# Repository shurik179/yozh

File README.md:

# Yozh Robot
Yozh is a small tracked  robot programmable in CircuitPython. 
It was  inspired by  Pololu's Zumo, but has numerous improvements over it. 
It was created by shurik179 for a robotics class at SigmaCamp.

The project description and logs are posted on Hackaday: 
https://hackaday.io/project/193665-yozh-robot. 
Detailed  user documentation is available at http://yozh.rtfd.io. 

## Status
Version 4 is mostly finished, working on documentation and fine-tuning 
various PID controllers. 

## Structure of this repository
* `docs`: documentation (used to produce docs at http://yozh.rtfd.io)
* `hardware`: design files for the custom electronics boards, BOM, etc.
* `board_support_package`: bootloader and packeg to have the secondary MCU 
   supported in Arduino IDE. Only needed fro uploading the firmware - end 
   users do not need this. 
* `firmware`: firmware for secondary MCU
* `circuitpython_library`: Circuit Python user library

## License
Ecept as noted below, all components (hardware, software, documentation) are
copyright by Alexander Kirillov  and are  released under MIT license.
See file LICENSE in this directory for full text of the license.

Circuit Python librabries included in circuitpython_library/lib are copyright by Adafruit, see
https://github.com/adafruit/Adafruit_CircuitPython_Bundle . They are released under MIT License.

Fonts included with Circuit Python library are released under SIL Open Font License.
See LICENSE file in directory circuitpython_library/fonts

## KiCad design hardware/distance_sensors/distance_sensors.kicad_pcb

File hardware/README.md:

# Hardware components for Yozh

This directory contains various hardware design files for Yozh. It includes
the following files and directories:

* `mainboard`: directory with design files for the main electronics board
* `spacer`: design files for the  spacer,  which goes between the main board and the chassis
* `reflectance_sensor_array`: design files for the reflectance sensor array   
* `top_plate`, `top_plate-LSM6`: design files for two different versions of the  
   top plate, containingin OLED display, buttons, and IMU. Current version of
   the robot uses `top_plate-LSM6`, which is based on LSM6DSL 6 degree of freedom
   Inertial Motion Unit.
   Folder `top_plate` contains design based on ICM42968 9DOF IMU; this is work in progress to be used in future versions.
* `front_sensors`: design files for  the removable board containing the two front-facing distance sensors
* `blade.dxf`: the DXF file of the front blade. This blade is to be lasercut
  from 0.030" stainless steel (you can use Pololu [laser-cutting service](https://www.pololu.com/product/749)  for it. )
* `pins.xlsx`: spreadsheet listing all pins of SAMD21 MCU and their use
* `board frame.stl`: STL file of the 3d printed holder I used to hold the mainboard
   for stenciling solder paste

Each design directory contains KiCad 6.0  design files, BOM, and gerbers.  
I assembled the mainboard myself; the top plate, reflectance sensor array, and front sensor board I ordered assembled from JLCPCB. These directories  have two versions of BOM: general and for JLCPCB assembly.

All PCBs use 1.6mm thickness, black soldermask and white screen. The main board
is a 4-layer PCB, all others are 2-layer.

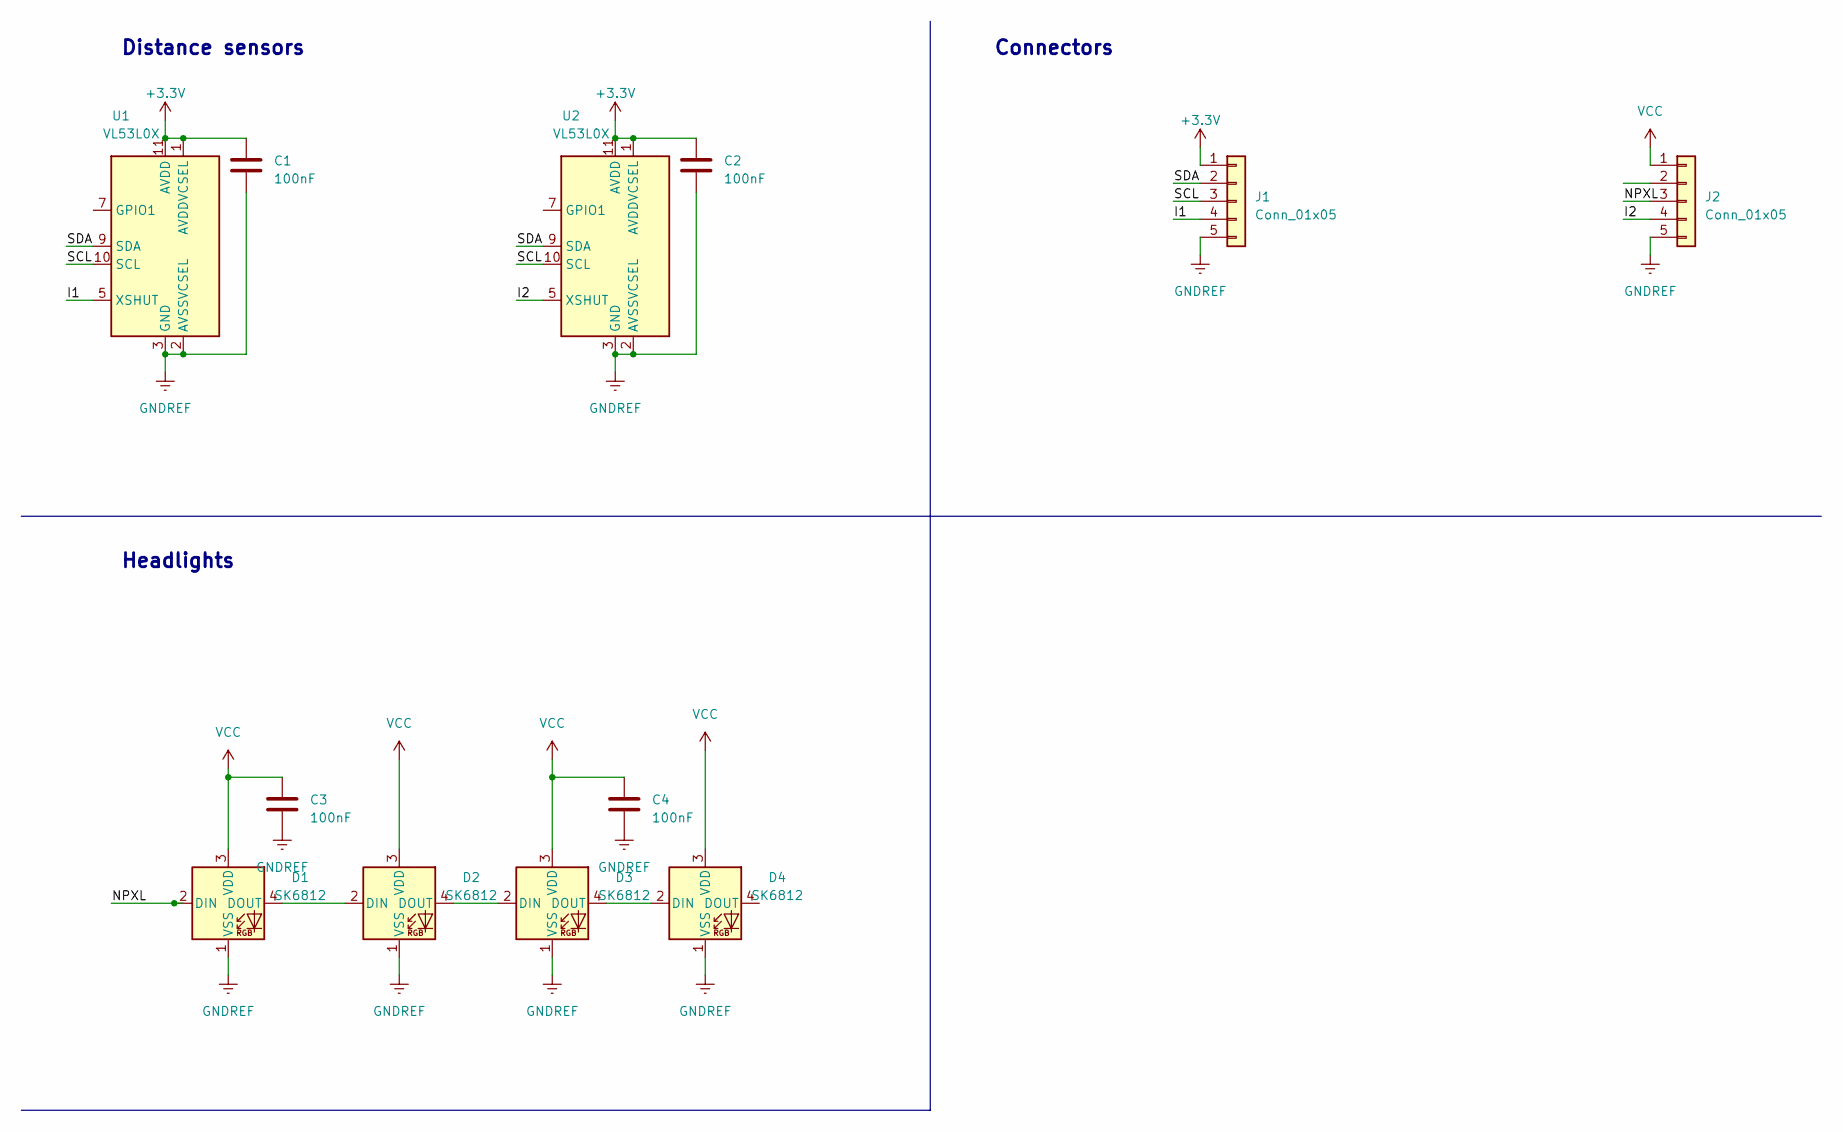
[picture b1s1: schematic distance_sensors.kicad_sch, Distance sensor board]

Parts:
C1, C2, C3, C4: 100nF; C_0603_1608Metric; LCSC C14663
D1, D2, D3, D4: SK6812; LED_SK6812_PLCC4_5.0x5.0mm_P3.2mm
J1, J2: Conn_01x05; PinSocket_1x05_P2.54mm_Vertical
U1, U2: VL53L0X; ST_VL53L1x; LCSC C91199

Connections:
+3V3: C1.1, C2.1, J1.1, U1.1 (AVDDVCSEL), U1.11 (AVDD), U2.1 (AVDDVCSEL), U2.11 (AVDD)
/I1: J1.4, U1.5 (XSHUT)
/I2: J2.4, U2.5 (XSHUT)
/NPXL: D1.2 (DIN), J2.3
/SCL: J1.3, U1.10 (SCL), U2.10 (SCL)
/SDA: J1.2, U1.9 (SDA), U2.9 (SDA)
GNDREF: C1.2, C2.2, C3.2, C4.2, D1.1 (VSS), D2.1 (VSS), D3.1 (VSS), D4.1 (VSS), J1.5, J2.5, U1.2 (AVSSVCSEL), U1.3 (GND), U1.4 (GND), U1.6 (GND), U1.12 (GND), U2.2 (AVSSVCSEL), U2.3 (GND), U2.4 (GND), U2.6 (GND), U2.12 (GND)
unnamed: D1.4 (DOUT), D2.2 (DIN)
unnamed: D2.4 (DOUT), D3.2 (DIN)
unnamed: D3.4 (DOUT), D4.2 (DIN)
VCC: C3.1, C4.1, D1.3 (VDD), D2.3 (VDD), D3.3 (VDD), D4.3 (VDD), J2.1

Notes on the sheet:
Distance sensors
Connectors
Headlights

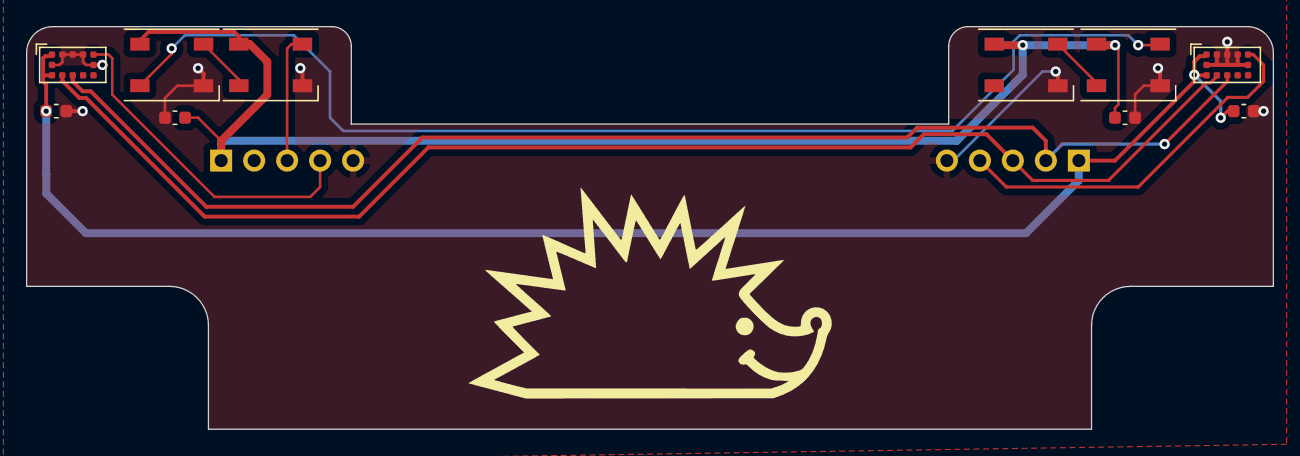
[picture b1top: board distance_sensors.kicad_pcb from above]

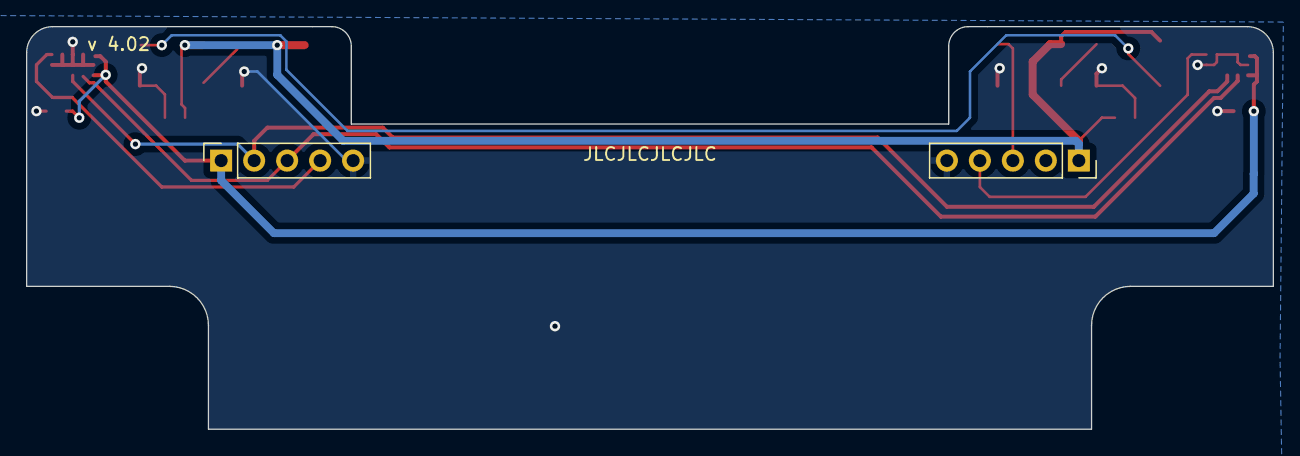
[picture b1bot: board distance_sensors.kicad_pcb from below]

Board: 2 copper layers, 96.0 x 31.0 mm, 12 parts (2 on the bottom side), 11 nets.

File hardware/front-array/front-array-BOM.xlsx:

Component | Description | Part Number | References | Value | Footprint | Quantity Per PCB | Side | Datasheet | LCSC | Comment
1 | SMD capacitor, 0603, 100nF |  | C1 C2 | 100nF | C_0603_1608Metric | 2 | Top | ~ | C14663
2 | 1x5 female header, 90 deg, 0.1" |  | J1 J2 | Conn_01x05 | PinSocket_1x05_P2.54mm_Horizontal | 2 | Top | ~
3 | 2m distance ranging ToF sensor | VL53L0X | U1 U2 | VL53L0X | LGA12 | 2 | Top | https://www.st.com/resource/en/datasheet/vl53l0x.pdf | C91199

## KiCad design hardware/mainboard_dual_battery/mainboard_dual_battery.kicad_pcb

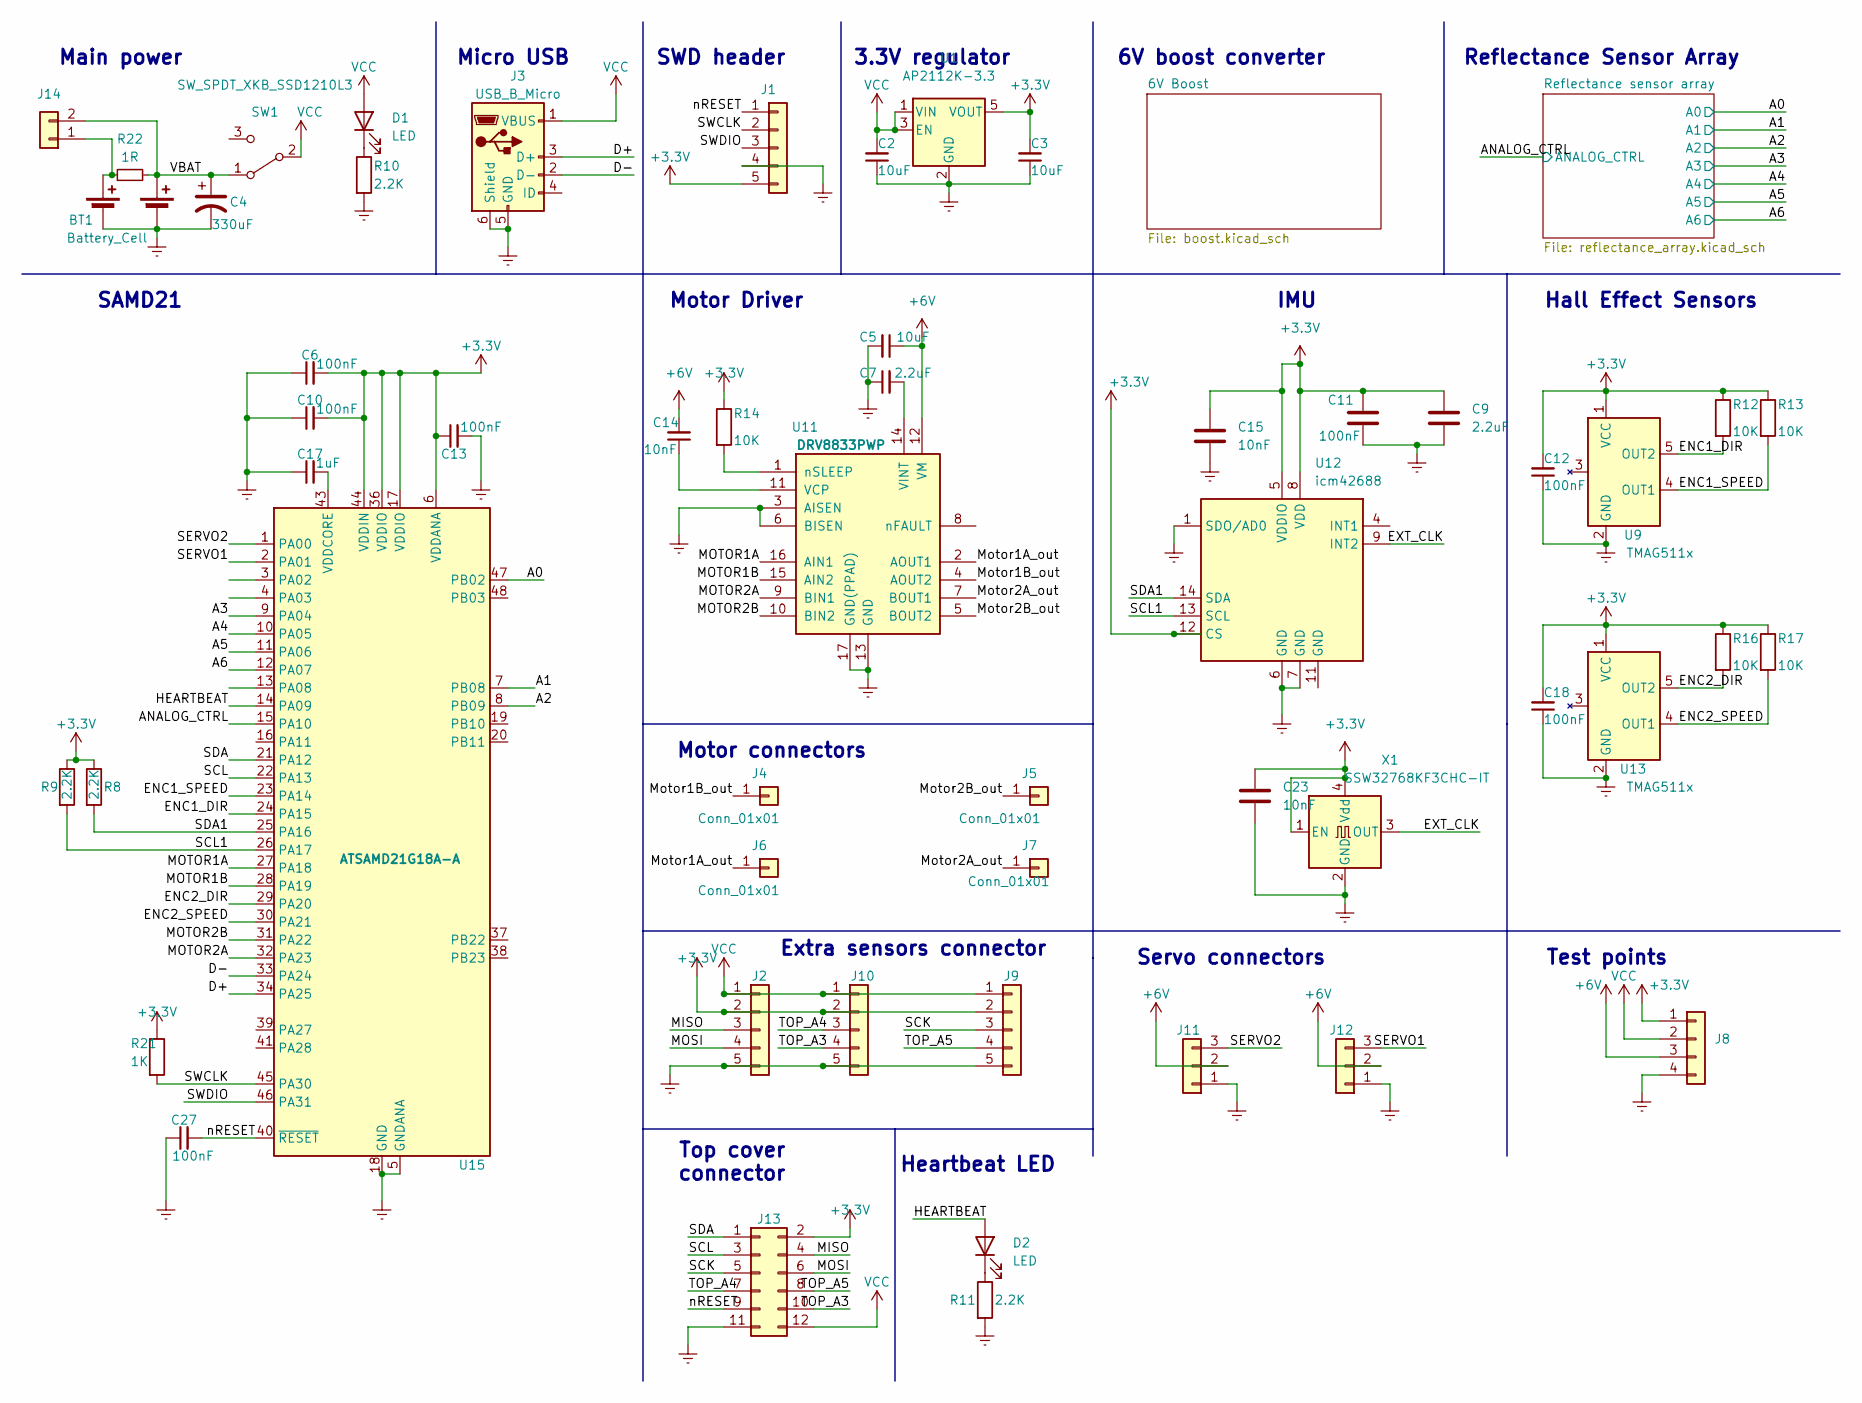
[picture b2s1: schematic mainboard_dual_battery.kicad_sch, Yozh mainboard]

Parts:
BT1: Battery_Cell; BatteryHolder_MYOUNG_BH-18650-B1BA007_2x18650; LCSC C6937126
C2, C3, C5: 10uF; C_0805_2012Metric; LCSC C15850
C4: 330uF; CP_Elec_6.3x7.7; LCSC C2980164
C6, C10, C11, C12, C13, C18, C27: 100nF; C_0603_1608Metric; LCSC C14663
C7, C9: 2.2uF; C_0603_1608Metric; LCSC C23630
C14, C15, C23: 10nF; C_0603_1608Metric; LCSC C57112
C17: 1uF; C_0603_1608Metric; LCSC C15849
D1, D2: LED; LED_0603_1608Metric; LCSC C72043
J1: Conn_01x05; PinSocket_1x05_P2.54mm_Lock
J2, J9, J10: Conn_01x05; PinHeader_1x05_P2.54mm_Vertical; LCSC C492404
J3: USB_B_Micro; USB_Micro-B_Amphenol_10118194_Horizontal; LCSC C132563
J4, J5, J6, J7: Conn_01x01; connector-1p-generic-nosilk
J8: Conn_01x04; connector-4p-generic-nosilk
J11, J12: Conn_01x03; PinHeader_1x03_P2.54mm_Vertical; LCSC C49257
J13: Conn_02x06_Odd_Even; PinSocket_2x06_P2.54mm_Vertical; LCSC C541855
J14: Conn_01x02; PinHeader_1x02_P2.54mm_Vertical
R8, R9, R10, R11: 2.2K; R_0603_1608Metric; LCSC C4190
R12, R13, R14, R16, R17: 10K; R_0603_1608Metric; LCSC C25804
R21: 1K; R_0603_1608Metric; LCSC C21190
R22: 1R; R_0603_1608Metric; LCSC C22936
SW1: SW_SPDT_XKB_SSD1210L3; SW_XKB_SS12D10L3; LCSC C319013
U1: AP2112K-3.3; SOT-23-5; LCSC C51118
U9, U13: TMAG511x; SOT-23-5
U11: DRV8833PWP; HTSSOP-16-1EP_4.4x5mm_P0.65mm_EP3.4x5mm_Mask2.46x2.31mm_The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; LCSC C50506
U12: icm42688; Bosch_LGA-14_3x2.5mm_P0.5mm; LCSC C1850418
U15: ATSAMD21G18A-A; QFP-48_7x7_Pitch0.5mm_reduced; LCSC C78624
X1: SSW32768KF3CHC-IT; Crystal_SMD_3225-4Pin_3.2x2.5mm_small_pads; LCSC C253931

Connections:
+3V3: C3.2, C6.2, C9.1, C10.2, C11.1, C12.2, C13.1, C15.1, C18.2, C23.1, J1.5, J2.2, J8.1, J9.2, J10.2, J13.2, R8.1, R9.1, R12.1, R13.1, R14.1, R16.1, R17.1, R21.1, U1.5 (VOUT), U9.1 (VCC), U12.5 (VDDIO), U12.8 (VDD), U12.12 (CS), U13.1 (VCC), U15.6 (VDDANA), U15.17 (VDDIO), U15.36 (VDDIO), U15.44 (VDDIN), X1.1 (EN), X1.4 (Vdd); also elsewhere on the board
/A0: U15.47 (PB02); also elsewhere on the board
/A1: U15.7 (PB08); also elsewhere on the board
/A2: U15.8 (PB09); also elsewhere on the board
/A3: U15.9 (PA04); also elsewhere on the board
/A4: U15.10 (PA05); also elsewhere on the board
/A5: U15.11 (PA06); also elsewhere on the board
/A6: U15.12 (PA07); also elsewhere on the board
/ANALOG_CTRL: U15.15 (PA10); also elsewhere on the board
/D+: J3.3 (D+), U15.34 (PA25)
/D-: J3.2 (D-), U15.33 (PA24)
/ENC1_DIR: R12.2, U9.5 (OUT2), U15.24 (PA15)
/ENC1_SPEED: R13.2, U9.4 (OUT1), U15.23 (PA14)
/ENC2_DIR: R16.2, U13.5 (OUT2), U15.29 (PA20)
/ENC2_SPEED: R17.2, U13.4 (OUT1), U15.30 (PA21)
/EXT_CLK: U12.9 (INT2), X1.3 (OUT)
/HEARTBEAT: D2.2 (A), U15.14 (PA09)
/MISO: J2.3, J13.4
/MOSI: J2.4, J13.6
/MOTOR1A: U11.16 (AIN1), U15.27 (PA18)
/MOTOR1B: U11.15 (AIN2), U15.28 (PA19)
/MOTOR2A: U11.9 (BIN1), U15.32 (PA23)
/MOTOR2B: U11.10 (BIN2), U15.31 (PA22)
/Motor1A_out: J6.1, U11.2 (AOUT1)
/Motor1B_out: J4.1, U11.4 (AOUT2)
/Motor2A_out: J7.1, U11.7 (BOUT1)
/Motor2B_out: J5.1, U11.5 (BOUT2)
/SCK: J9.3, J13.5
/SCL: J13.3, U15.22 (PA13)
/SCL1: R9.2, U12.13 (SCL), U15.26 (PA17)
/SDA: J13.1, U15.21 (PA12)
/SDA1: R8.2, U12.14 (SDA), U15.25 (PA16)
/SERVO1: J12.3, U15.2 (PA01)
/SERVO2: J11.3, U15.1 (PA00)
/SWCLK: J1.2, R21.2, U15.45 (PA30)
/SWDIO: J1.3, U15.46 (PA31)
/TOP_A3: J10.4, J13.10
/TOP_A4: J10.3, J13.7
/TOP_A5: J9.4, J13.8
/VBAT: BT1.3 (+), C4.1, J14.2, R22.2, SW1.1 (A)
/nRESET: C27.2, J1.1, J13.9, U15.40 (~RESET)
GNDREF: BT1.2 (-), BT1.4 (-), C2.1, C3.1, C4.2, C5.2, C6.1, C7.1, C9.2, C10.1, C11.2, C12.1, C13.2, C15.2, C17.1, C18.1, C23.2, C27.1, J1.4, J2.5, J3.5 (GND), J3.6 (Shield), J8.4, J9.5, J10.5, J11.1, J12.1, J13.11, R10.2, R11.2, U1.2 (GND), U9.2 (GND), U11.3 (AISEN), U11.6 (BISEN), U11.13 (GND), U11.17 (GND(PPAD)), U12.1 (SDO/AD0), U12.6 (GND), U12.7 (GND), U13.2 (GND), U15.5 (GNDANA), U15.18 (GND), U15.35 (GND), U15.42 (GND), X1.2 (GND); also elsewhere on the board
unnamed: D1.1 (K), R10.1
unnamed: D2.1 (K), R11.1
unnamed: BT1.1 (+), J14.1, R22.1
unnamed: C14.1, U11.11 (VCP)
unnamed: C7.2, U11.14 (VINT)
unnamed: R14.2, U11.1 (nSLEEP)
unnamed: C17.2, U15.43 (VDDCORE)

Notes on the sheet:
Hall Effect Sensors
IMU
6V boost converter
SWD header
3.3V regulator
Top cover connector
Servo connectors
Extra sensors connector
Motor Driver
SAMD21
Heartbeat LED
Main power
Motor connectors
Reflectance Sensor Array
Test points
Micro USB

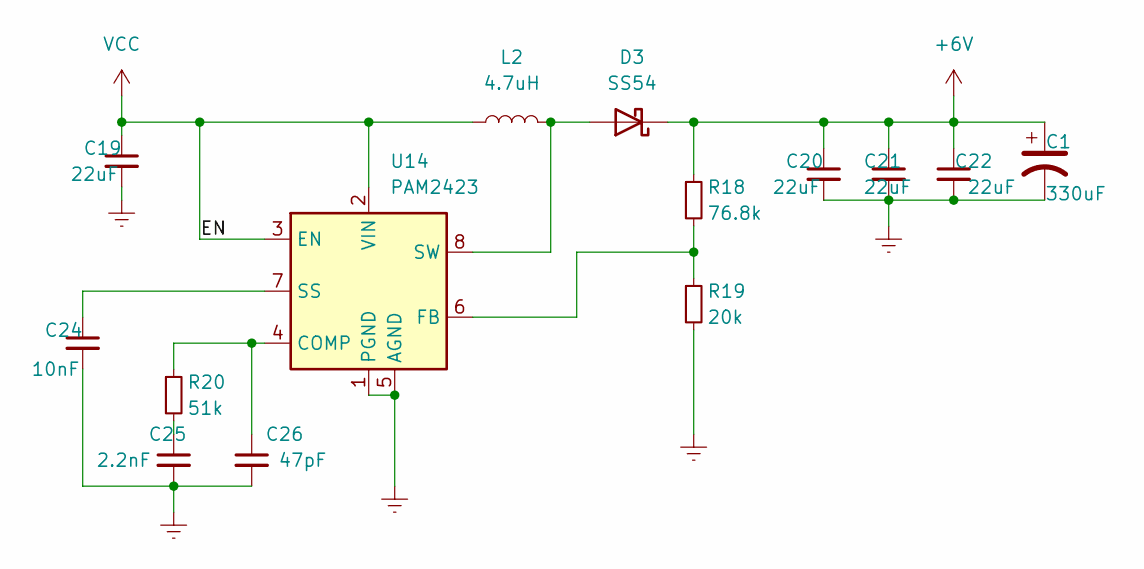
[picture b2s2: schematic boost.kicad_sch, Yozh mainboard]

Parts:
C1: 330uF; CP_Elec_6.3x7.7; LCSC C2980164
C19, C20, C21, C22: 22uF; C_0805_2012Metric; LCSC C45783
C24: 10nF; C_0603_1608Metric; LCSC C57112
C25: 2.2nF; C_0603_1608Metric; LCSC C1604
C26: 47pF; C_0603_1608Metric; LCSC C1671
D3: SS54; D_SMA; LCSC C22452
L2: 4.7uH; L_Panasonic-ETQP3M; LCSC C412309
R18: 76.8k; R_0603_1608Metric; LCSC C165743
R19: 20k; R_0603_1608Metric; LCSC C4184
R20: 51k; R_0603_1608Metric; LCSC C23196
U14: PAM2423; SOIC-8-1EP_3.9x4.9mm_P1.27mm_EP2.62x3.51mm; LCSC C781891

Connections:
GNDREF: C1.2, C19.2, C20.2, C21.2, C22.2, C24.2, C25.2, C26.2, R19.2, U14.1 (PGND), U14.5 (AGND); also elsewhere on the board
unnamed: C25.1, R20.2
unnamed: D3.2 (A), L2.2, U14.8 (SW)
unnamed: C26.1, R20.1, U14.4 (COMP)
unnamed: R18.2, R19.1, U14.6 (FB)
unnamed: C24.1, U14.7 (SS)

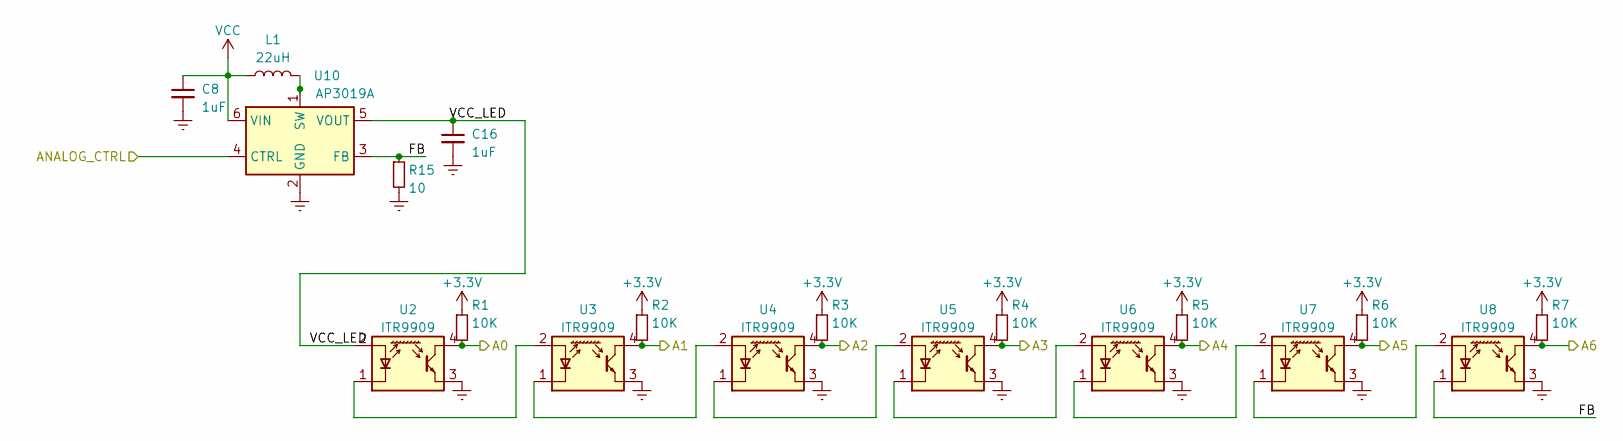
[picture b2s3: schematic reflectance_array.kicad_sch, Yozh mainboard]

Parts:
C8, C16: 1uF; C_0603_1608Metric; LCSC C15849
L1: 22uH; L_Taiyo-Yuden_NR-40xx; LCSC C2880384
R1, R2, R3, R4, R5, R6, R7: 10K; R_0603_1608Metric; LCSC C25804
R15: 10; R_0603_1608Metric; LCSC C319921
U2, U3, U4, U5, U6, U7, U8: ITR9909; Everlight_ITR9909; LCSC C53399
U10: AP3019A; TSOT-23-6; LCSC C44956

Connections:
+3V3: R1.1, R2.1, R3.1, R4.1, R5.1, R6.1, R7.1; also elsewhere on the board
/A0: R1.2, U2.4 (C); also elsewhere on the board
/A1: R2.2, U3.4 (C); also elsewhere on the board
/A2: R3.2, U4.4 (C); also elsewhere on the board
/A3: R4.2, U5.4 (C); also elsewhere on the board
/A4: R5.2, U6.4 (C); also elsewhere on the board
/A5: R6.2, U7.4 (C); also elsewhere on the board
/A6: R7.2, U8.4 (C); also elsewhere on the board
/ANALOG_CTRL: U10.4 (CTRL); also elsewhere on the board
/Reflectance sensor array/FB: R15.1, U8.1 (K), U10.3 (FB)
/Reflectance sensor array/VCC_LED: C16.1, U2.2 (A), U10.5 (VOUT)
GNDREF: C8.2, C16.2, R15.2, U2.3 (E), U3.3 (E), U4.3 (E), U5.3 (E), U6.3 (E), U7.3 (E), U8.3 (E), U10.2 (GND); also elsewhere on the board
unnamed: U2.1 (K), U3.2 (A)
unnamed: U3.1 (K), U4.2 (A)
unnamed: U4.1 (K), U5.2 (A)
unnamed: U5.1 (K), U6.2 (A)
unnamed: U6.1 (K), U7.2 (A)
unnamed: U7.1 (K), U8.2 (A)
unnamed: L1.2, U10.1 (SW)

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
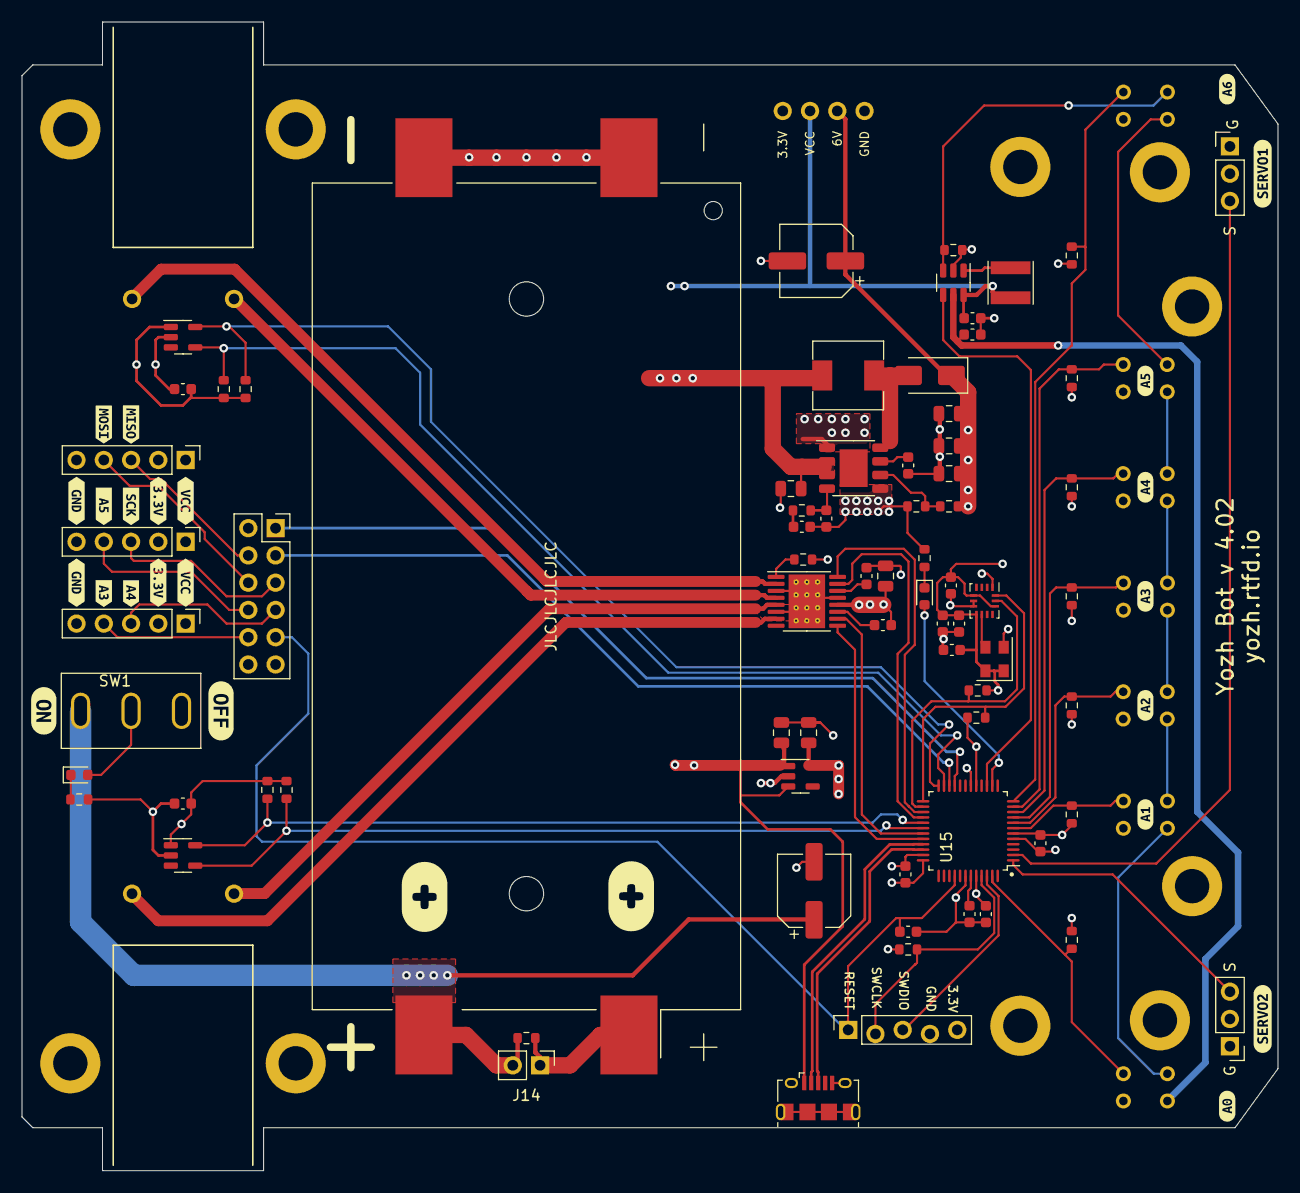
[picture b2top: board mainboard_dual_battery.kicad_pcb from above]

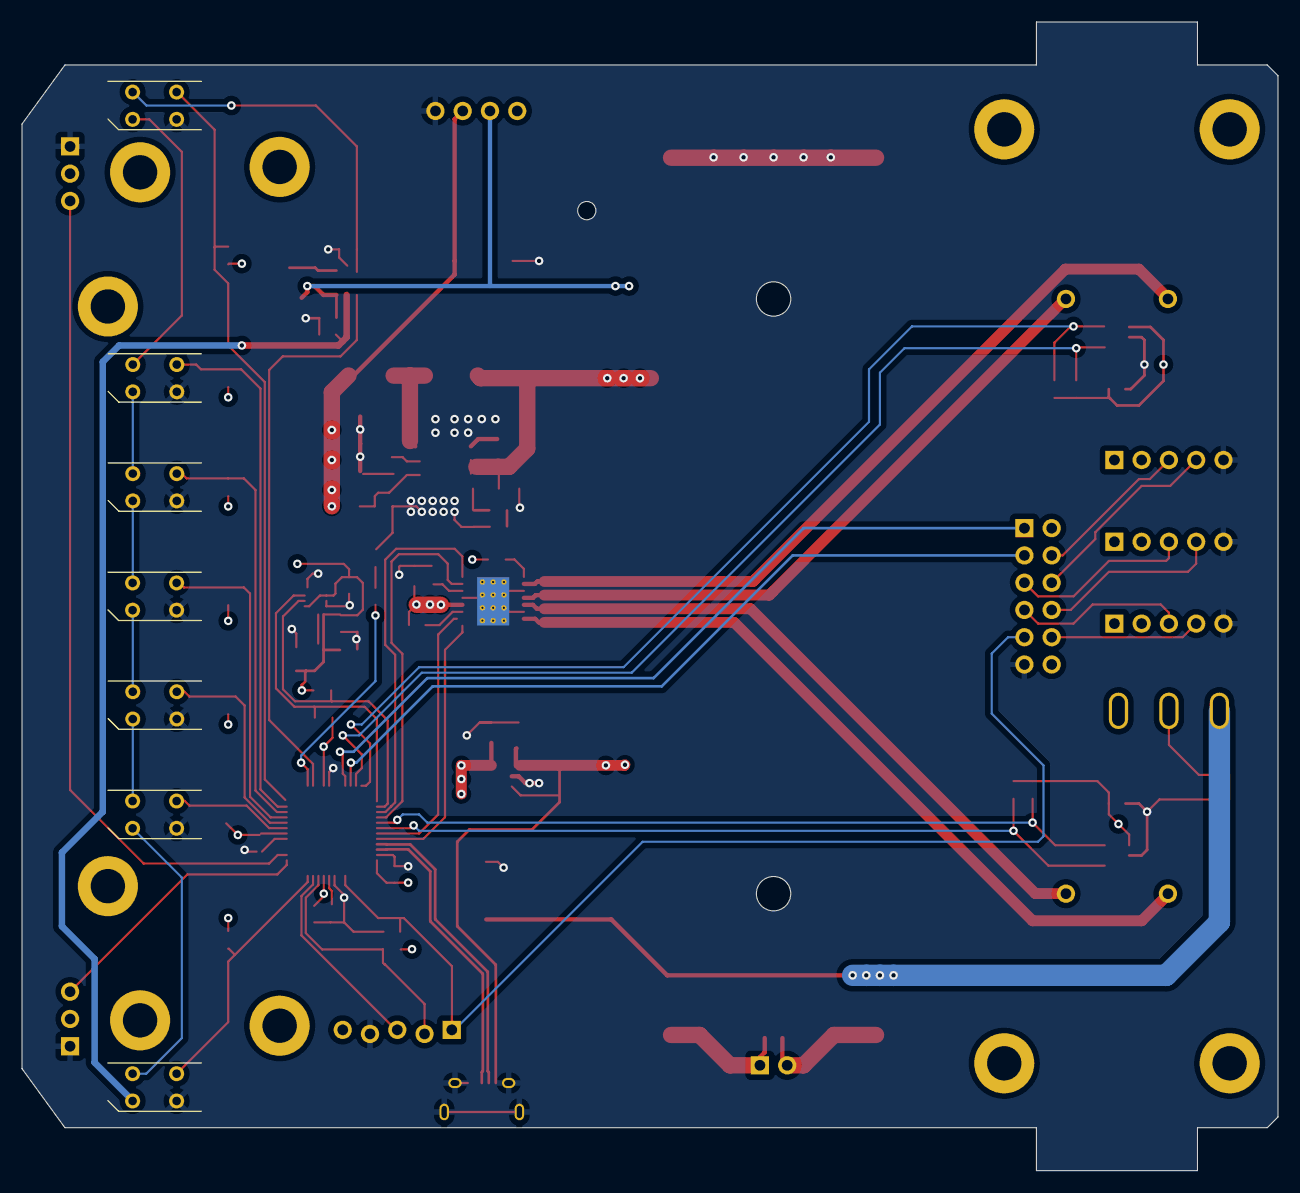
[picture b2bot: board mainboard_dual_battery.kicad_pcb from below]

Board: 4 copper layers, 117.0 x 107.0 mm, 111 parts (7 on the bottom side), 65 nets.

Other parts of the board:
kibuzzard-653BD0CB: G***; kibuzzard-653BD0CB
kibuzzard-653BD1D9: G***; kibuzzard-653BD1D9
kibuzzard-653BD1F8: G***; kibuzzard-653BD1F8
kibuzzard-653BD3E9, kibuzzard-653BD3E9#2: G***; kibuzzard-653BD3E9
kibuzzard-653BD5EB: G***; kibuzzard-653BD5EB
kibuzzard-653BD15F: G***; kibuzzard-653BD15F
kibuzzard-653BD22E: G***; kibuzzard-653BD22E
kibuzzard-653BD101: G***; kibuzzard-653BD101
kibuzzard-653BD134: G***; kibuzzard-653BD134
kibuzzard-653BD153: G***; kibuzzard-653BD153
kibuzzard-653BD166: G***; kibuzzard-653BD166
kibuzzard-653BD170: G***; kibuzzard-653BD170
kibuzzard-653BD252: G***; kibuzzard-653BD252
kibuzzard-653BD666: G***; kibuzzard-653BD666
kibuzzard-653BDAE1: G***; kibuzzard-653BDAE1
kibuzzard-653BDB0C: G***; kibuzzard-653BDB0C
kibuzzard-653BDB2A: G***; kibuzzard-653BDB2A
kibuzzard-653BDB3F: G***; kibuzzard-653BDB3F
kibuzzard-653BDB4D: G***; kibuzzard-653BDB4D
kibuzzard-653BDB7B: G***; kibuzzard-653BDB7B
kibuzzard-653BDB20: G***; kibuzzard-653BDB20
kibuzzard-653BDB31: G***; kibuzzard-653BDB31
kibuzzard-653BDB46: G***; kibuzzard-653BDB46
kibuzzard-653BDB91: G***; kibuzzard-653BDB91

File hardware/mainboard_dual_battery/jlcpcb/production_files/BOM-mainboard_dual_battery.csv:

Comment,Designator,Footprint,LCSC
USB_B_Micro,J3,USB_Micro-B_Amphenol_10118194_Horizontal,C132563
100nF,"C10,C11,C12,C13,C18,C27,C6",C_0603_1608Metric,C14663
1uF,"C16,C17,C8",C_0603_1608Metric,C15849
10uF,"C2,C3,C5",C_0805_2012Metric,C15850
2.2nF,C25,C_0603_1608Metric,C1604
76.8k,R18,R_0603_1608Metric,C165743
47pF,C26,C_0603_1608Metric,C1671
icm42688,U12,Bosch_LGA-14_3x2.5mm_P0.5mm,C1850418
1K,R21,R_0603_1608Metric,C21190
SS54,D3,D_SMA,C22452
1R,R22,R_0603_1608Metric,C22936
51k,R20,R_0603_1608Metric,C23196
2.2uF,"C7,C9",C_0603_1608Metric,C23630
SSW32768KF3CHC-IT,X1,Crystal_SMD_3225-4Pin_3.2x2.5mm_small_pads,C253931
10K,"R1,R12,R13,R14,R16,R17,R2,R3,R4,R5,R6,R7",R_0603_1608Metric,C25804
22uH,L1,L_Taiyo-Yuden_NR-40xx,C2880384
330uF,"C19,C4",CP_Elec_6.3x7.7,C2980164
SW_SPDT_XKB_SSD1210L3,SW1,SW_XKB_SS12D10L3,C319013
10,R15,R_0603_1608Metric,C319921
4.7uH,L2,L_Panasonic-ETQP3M,C412309
20k,R19,R_0603_1608Metric,C4184
2.2K,"R10,R11,R8,R9",R_0603_1608Metric,C4190
AP3019A,U10,TSOT-23-6,C44956
22uF,"C1,C20,C21,C22",C_0805_2012Metric,C45783
Conn_01x05,"J10,J2,J9",PinHeader_1x05_P2.54mm_Vertical,C492404
Conn_01x03,"J11,J12",PinHeader_1x03_P2.54mm_Vertical,C49257
DRV8833PWP,U11,HTSSOP-16-1EP_4.4x5mm_P0.65mm_EP3.4x5mm_Mask2.46x2.31mm_ThermalVias_reduced,C50506
AP2112K-3.3,U1,SOT-23-5,C51118
ITR9909,"U2,U3,U4,U5,U6,U7,U8",Everlight_ITR9909,C53399
Conn_02x06_Odd_Even,J13,PinSocket_2x06_P2.54mm_Vertical,C541855
10nF,"C14,C15,C23,C24",C_0603_1608Metric,C57112
Battery_Cell,BT1,BatteryHolder_MYOUNG_BH-18650-B1BA007_2x18650,C6937126
LED,"D1,D2",LED_0603_1608Metric,C72043
PAM2423,U14,SOIC-8-1EP_3.9x4.9mm_P1.27mm_EP2.62x3.51mm,C781891
ATSAMD21G18A-A,U15,QFP-48_7x7_Pitch0.5mm_reduced,C78624

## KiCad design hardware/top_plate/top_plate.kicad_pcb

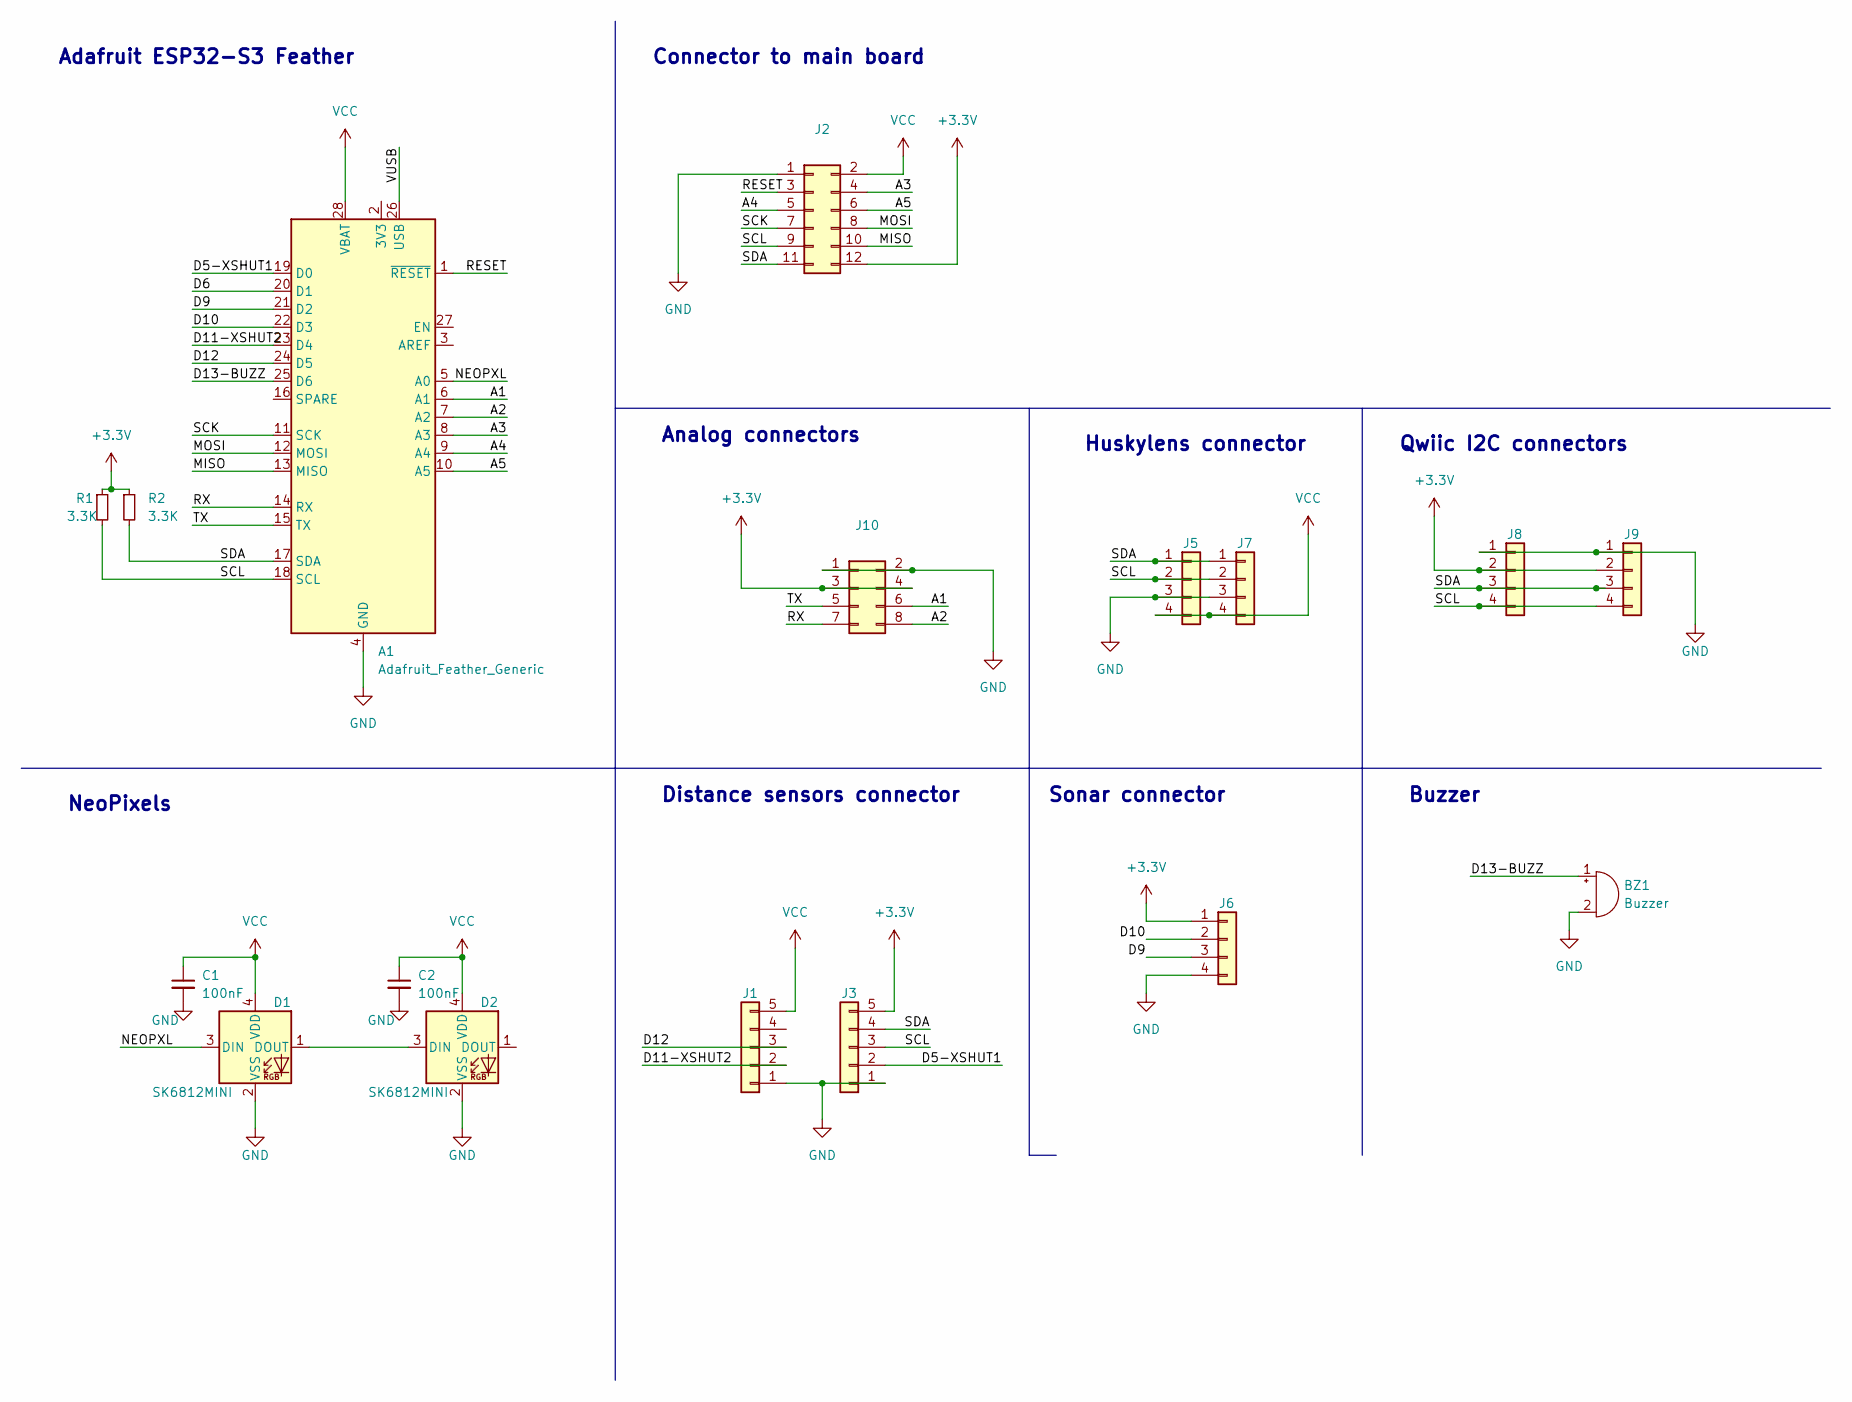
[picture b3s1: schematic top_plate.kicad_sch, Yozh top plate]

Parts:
A1: Adafruit_Feather_Generic; Adafruit_Feather
BZ1: Buzzer; Buzzer_TDK_PS1240P02BT_D12.2mm_H6.5mm
C1, C2: 100nF; C_0603_1608Metric; LCSC C14663
D1, D2: SK6812MINI; LED_SK6812MINI_PLCC4_3.5x3.5mm_P1.75mm; LCSC C2886570
J1, J3: Conn_01x05; PinHeader_1x05_P2.54mm_Horizontal
J2: Conn_02x06_Odd_Even; PinSocket_2x06_P2.54mm_Vertical
J5: Conn_01x04; JST_PH_B4B-PH-K_1x04_P2.00mm_Vertical; LCSC C131334
J6: Conn_01x04; connector-4p-generic-nosilk
J7: Conn_01x04; connector-4p-generic-nosilk; LCSC C2691448
J8, J9: Conn_01x04; JST_SH_BM04B-SRSS-TB_1x04-1MP_P1.00mm_Vertical; LCSC C160390
J10: Conn_02x04_Odd_Even; PinHeader_2x04_P2.54mm_Vertical
R1, R2: 3.3K; R_0603_1608Metric; LCSC C22978

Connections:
+3V3: J2.12, J3.5, J6.1, J8.2, J9.2, J10.3, J10.4, R1.1, R2.1
/A1: A1.6 (A1), J10.6
/A2: A1.7 (A2), J10.8
/A3: A1.8 (A3), J2.4
/A4: A1.9 (A4), J2.5
/A5: A1.10 (A5), J2.6
/D5-XSHUT1: A1.19 (D0), J3.2
/D6: A1.20 (D1)
/D9: A1.21 (D2), J6.3
/D10: A1.22 (D3), J6.2
/D11-XSHUT2: A1.23 (D4), J1.2
/D12: A1.24 (D5), J1.3
/D13-BUZZ: A1.25 (D6), BZ1.1 (-)
/MISO: A1.13 (MISO), J2.10
/MOSI: A1.12 (MOSI), J2.8
/NEOPXL: A1.5 (A0), D1.3 (DIN)
/RESET: A1.1 (~RESET), J2.3
/RX: A1.14 (RX), J10.7
/SCK: A1.11 (SCK), J2.7
/SCL: A1.18 (SCL), J2.9, J3.3, J5.2, J7.2, J8.4, J9.4, R1.2
/SDA: A1.17 (SDA), J2.11, J3.4, J5.1, J7.1, J8.3, J9.3, R2.2
/TX: A1.15 (TX), J10.5
/VUSB: A1.26 (USB)
GND: A1.4 (GND), BZ1.2 (+), C1.2, C2.2, D1.2 (VSS), D2.2 (VSS), J1.1, J2.1, J3.1, J5.3, J6.4, J7.3, J8.1, J9.1, J10.1, J10.2
unnamed: D1.1 (DOUT), D2.3 (DIN)
VCC: A1.28 (VBAT), C1.1, C2.1, D1.4 (VDD), D2.4 (VDD), J1.5, J2.2, J5.4, J7.4

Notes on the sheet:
Analog connectors
Buzzer
Adafruit ESP32-S3 Feather
Distance sensors connector
NeoPixels
Sonar connector
Huskylens connector
Connector to main board
Qwiic I2C connectors

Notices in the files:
parts and their libraries:
LICENSE: MIT License
